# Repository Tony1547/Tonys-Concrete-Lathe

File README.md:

# Tonys-Concrete-Lathe #
Lathe but 3d prints &amp; concrete

Special thanks Mark Harris to for creating this open source design which I based my H-brdge motor driver off of, heres the link to his blog of his design and his git hub page:

- https://resources.altium.com/p/100a-12v-h-bridge-project

- https://github.com/issus

and another big thanks to Chris Borge for inspiring this project with his "I Printed A Better Lathe" video

- https://www.youtube.com/watch?v=6Js8erWbsDQ

---- 

This is the lathe I have been desingning for the past 2-ish months, I was initially inspired by Chris Borge a Youtuber who focuses on creating machines to help with his own personal projects and 3d-prints that are filled with concrete. Now, this is the second iteration design, not becuase I built a first lathe but because the first time I tried to put everything into CAD it all started to look like a toy and I thought I could do better, which I'm glad that I did. Which now leads to the vesion you see above and below this bar of text.

Something I initially struggled with was finding a way to connect all the parts toghether, in my initial design I tried to make each 3d printed part interlock with dove-tails but that soon became much more problematic than was needed. I solved this problem with allowing an open hole from part to part on the inside to connect all parts into this chamber that I hope keeps everything together once the concrete dries. 

For the reason that I built this project, I want to have better manufacturing capabilities at home, and having a machine that allows me to focus on one type of part (being conical and cylindrical parts) I think will allow me to have better projects in the future.

Journal: https://fallout.hackclub.com/projects/1831

# Assembly
Hi! if you're reading this, your either reading to review, see whats going on, or interested in building this project yourself.

- The first step in creating the lathe is set up, make sure you have all hardware, bearings, belt &amp; pulley's, 3d prints, PCB, concrete, and extrusion material on hand

- Make sure to use heated inserts before this next step and to cover anny holes which may clog with concrete with tape.

- The next step is is to assemble the base, head stock, and upper walls seperately, glue them with each other inside those groups and let it rest (you may want to put the hardware, extrusions, and linear slide in for the base before glueing), after the glue is done drying, you may start off by pouring concrete into the base.

- After concrete has been poured into the base (process can change depending on the part) you can now assemble and put-in the top of the lathe wall and headstock and fill those with conctete as well, if you can find a power tool to vibrate the lathe to allow air bubbles to escape then use that as well too.

-After allowing the concrete to dry, you may add on the tool carriage and screw on the PCB to to the lathe, make sure to wire and test and you should have a functional lathe!

Remember when using the lathe, the part should be spining to where it's coming down onto the tool and not the other way around.

Currently the lathe is run by either two buttons on the back for foward/revevrse but the option for external control was also given, so with an off board micro controller you could be very exact with how you want this thing to spin. (I plan to use an off board MCU when possible)

Onshape: https://cad.onshape.com/documents/8fec9f06f8e21e4e1cabcead/w/11b83efad18e13bc0ea2df61/e/2ea9e03e0bad05dbdf986923?page=2&email=ah404751%40g.risd.org&renderMode=0&uiState=6a30d3e5ff79be115d0b7c52

# BOM

Google Sheet: https://docs.google.com/spreadsheets/d/1Rf3SECQ2E7oCPYBzGCeOMEVJCDXd7yVN8Rsrsj5uyMo/edit?usp=sharing 

| Index   | Vendor      | Description                        | Quantity                  | Unit Price($)             | Extended Price($) | Product Link                                                                                                                                                                                                                                                                                                                                                                                                                                                                                                                                                                                                                                                         |      |          |     |          |               |                   |                                                    |
|---------|-------------|------------------------------------|---------------------------|---------------------------|-------------------|----------------------------------------------------------------------------------------------------------------------------------------------------------------------------------------------------------------------------------------------------------------------------------------------------------------------------------------------------------------------------------------------------------------------------------------------------------------------------------------------------------------------------------------------------------------------------------------------------------------------------------------------------------------------|------|----------|-----|----------|---------------|-------------------|----------------------------------------------------|
| 1       | Ali Express | 5x13x4mm Flanged Bearing           | 10                        | $0.51                     | $5.06             | https://www.aliexpress.us/item/3256803908686248.html?spm=a2g0o.productlist.main.1.596dOhTVOhTVzT&algo_pvid=de089ae8-5913-49c9-acd4-66d24c447885&algo_exp_id=de089ae8-5913-49c9-acd4-66d24c447885-0&pdp_ext_f=%7B%22order%22%3A%22852%22%2C%22eval%22%3A%221%22%2C%22fromPage%22%3A%22search%22%7D&pdp_npi=6%40dis%21USD%215.08%210.99%21%21%215.08%210.99%21%402101e8f317815960924911388ed342%2112000028970871486%21sea%21US%216805647519%21ABX%211%210%21n_tag%3A-29910%3Bd%3A3a14889%3Bm03_new_user%3A-29895%3BpisId%3A5000000207262921&curPageLogUid=q1H4CezHkX5N&utparam-url=scene%3Asearch%7Cquery_from%3A%7Cx_object_id%3A1005004095001000%7C_p_origin_prod%3A |      |          |     |          |               |                   |                                                    |
| 2       | Ali Express | 140T GT2 10mm belt                 | 1                         | $3.78                     | $3.78             | https://www.aliexpress.us/item/3256806906134014.html?spm=a2g0o.detail.0.0.6dc6bKhdbKhdvN&mp=1&pdp_npi=6%40dis%21USD%21USD+3.78%21USD+3.78%21%21USD+3.78%21%21%21%402101e2b017815961262145354ef2ca%2112000039378829177%21ct%21US%216805647519%21%211%210%21&gatewayAdapt=glo2usa                                                                                                                                                                                                                                                                                                                                                                                      |      |          |     |          |               |                   |                                                    |
| 3       | Ali Express | ER25 8mm Collet                    | 1                         | $6.25                     | $6.25             | https://www.aliexpress.us/item/2255800773550976.html?spm=a2g0o.detail.0.0.2c62U9tFU9tFKE&mp=1&pdp_npi=6%40dis%21USD%21USD+14.89%21USD+6.25%21%21USD+6.25%21%21%21%402101e07217815966367485977edac3%2110000012670797470%21ct%21US%216805647519%21%211%210%21&gatewayAdapt=glo2usa                                                                                                                                                                                                                                                                                                                                                                                     |      |          |     |          |               |                   |                                                    |
| 4       | Ali Express | 50mm Chuck                         | 1                         | $20.01                    | $20.01            | https://www.aliexpress.us/item/3256809251348831.html?spm=a2g0o.detail.0.0.6816AbePAbeP4V&mp=1&pdp_npi=6%40dis%21USD%21USD+40.01%21USD+20.01%21%21USD+20.01%21%21%21%402101e07217815966813736979edac3%2112000049098833905%21ct%21US%216805647519%21%211%210%21&gatewayAdapt=glo2usa                                                                                                                                                                                                                                                                                                                                                                                   |      |          |     |          |               |                   |                                                    |
| 5       | Ali Express | 30T + 60T Pulley's                 | 2                         | $9.47                     | $18.94            | https://www.aliexpress.us/item/3256805897449052.html?spm=a2g0o.detail.0.0.3809lnEelnEeAL&mp=1&pdp_npi=6%40dis%21USD%21USD+31.56%21USD+18.94%21%21USD+18.94%21%21%21%402101e07217815967189997474edac3%2112000035654690827%21ct%21US%216805647519%21%211%210%21&gatewayAdapt=glo2usa                                                                                                                                                                                                                                                                                                                                                                                   |      |          |     |          |               |                   |                                                    |
| 6       | Ali Express | 20x47x19.25 Tapered Roller Bearing | 2                         | $3.59                     | $7.18             | https://www.aliexpress.us/item/3256802472132854.html?spm=a2g0o.detail.0.0.54d2qkcUqkcUjC&mp=1&pdp_npi=6%40dis%21USD%21USD+11.04%21USD+7.18%21%21USD+7.18%21%21%21%402101e07217815967512357791edac3%2112000021590990791%21ct%21US%216805647519%21%211%210%21&gatewayAdapt=glo2usa                                                                                                                                                                                                                                                                                                                                                                                     |      |          |     |          |               |                   |                                                    |
| 7       | Ali Express | C20-ER25-150L Spindle              | 1                         | $15.84                    | $15.84            | https://www.aliexpress.us/item/3256801168631119.html?spm=a2g0o.detail.0.0.a1caNKVQNKVQHK&mp=1&pdp_npi=6%40dis%21USD%21USD+26.40%21USD+15.84%21%21USD+15.84%21%21%21%402101e07217815967927098166edac3%2112000025664963300%21ct%21US%216805647519%21%211%210%21&gatewayAdapt=glo2usa                                                                                                                                                                                                                                                                                                                                                                                   |      |          |     |          |               |                   |                                                    |
| 8       | Tnutz       | 2020 Extrusion                     | 2                         | $1.33                     | $2.66             | https://www.tnutz.com/product/exm-2020/?attribute_pa_length-in=12&attribute_pa_fractional-length=0-000                                                                                                                                                                                                                                                                                                                                                                                                                                                                                                                                                               |      |          |     |          |               |                   |                                                    |
| 9       | Tnutz       | Tapped 2020 Extrusion              | 2                         | $0.77                     | $1.54             | https://www.tnutz.com/product/exm-2020/?attribute_pa_length-in=3&attribute_pa_fractional-length=0-938-15-16                                                                                                                                                                                                                                                                                                                                                                                                                                                                                                                                                          |      |          |     |          |               |                   |                                                    |
| 10      | Tnutz       | M3 T-Nut                           | 40                        | $0.40                     | $16.00            | https://www.tnutz.com/product/st-020/?attribute_pa_thread-size=m3-x-0-5                                                                                                                                                                                                                                                                                                                                                                                                                                                                                                                                                                                              |      |          |     |          |               |                   |                                                    |
| 11      | Grainger    | 1M M4 Threaded Rod                 | 1                         | $2.35                     | $2.35             | https://www.grainger.com/product/Fully-Threaded-Rod-M4x0-70-25DM24                                                                                                                                                                                                                                                                                                                                                                                                                                                                                                                                                                                                   |      |          |     |          |               |                   |                                                    |
| 12      | Grainger    | M4 Nuts                            | 100                       | $0.03                     | $2.94             | https://www.grainger.com/product/Hex-Nut-Std-Hex-6CA71                                                                                                                                                                                                                                                                                                                                                                                                                                                                                                                                                                                                               |      |          |     |          |               |                   |                                                    |
| 13      | Amazon      | M3 Nuts                            | 150                       | $0.03                     | $4.99             | https://www.amazon.com/gp/product/B08N68W9SP/ref=ox_sc_act_title_1?smid=A2BPIUS9TNF8L5&psc=1                                                                                                                                                                                                                                                                                                                                                                                                                                                                                                                                                                         |      |          |     |          |               |                   |                                                    |
| 14      | Amazon      | 2 Part Epoxy                       | 1                         | $5.97                     | $5.97             | https://www.amazon.com/gp/product/B001Z3C3AG/ref=ox_sc_act_title_2?smid=ATVPDKIKX0DER&psc=1                                                                                                                                                                                                                                                                                                                                                                                                                                                                                                                                                                          |      |          |     |          |               |                   |                                                    |
| 15      | Amazon      | M3 Brass Inserts                   | 100                       | $0.05                     | $4.99             | https://www.amazon.com/gp/product/B0FM45X5TD/ref=ox_sc_act_title_3?smid=AIMQC13A5VC4X&psc=1                                                                                                                                                                                                                                                                                                                                                                                                                                                                                                                                                                          |      |          |     |          |               |                   |                                                    |
| 16      | Amazon      | M4 Brass Inserts                   | 60                        | $0.08                     | $4.83             | https://www.amazon.com/gp/product/B0DFWVT6XT/ref=ox_sc_act_title_4?smid=A3FX0IVQQTIB98&psc=1                                                                                                                                                                                                                                                                                                                                                                                                                                                                                                                                                                         |      |          |     |          |               |                   |                                                    |
| 17      | Amazon      | M3x10mm Screws                     | 120                       | $0.03                     | $3.79             | https://www.amazon.com/gp/product/B0F7LKRV5G/ref=ox_sc_act_title_5?smid=A2W3XYA7BVZZ2U&psc=1                                                                                                                                                                                                                                                                                                                                                                                                                                                                                                                                                                         |      |          |     |          |               |                   |                                                    |
| 18      | Amazon      | M3x25mm Screws                     | 40                        | $0.16                     | $6.39             | https://www.amazon.com/gp/product/B08R8J3175/ref=ox_sc_act_title_6?smid=A2XHUR0CG3X852&psc=1                                                                                                                                                                                                                                                                                                                                                                                                                                                                                                                                                                         |      |          |     |          |               |                   |                                                    |
| 19      | Amazon      | M3x22mm Screws                     | 50                        | $0.13                     | $6.29             | https://www.amazon.com/gp/product/B0FLYG7WZ7/ref=ox_sc_act_title_7?smid=A2SQCOYQC9C41K&psc=1                                                                                                                                                                                                                                                                                                                                                                                                                                                                                                                                                                         |      |          |     |          |               |                   |                                                    |
| 20      | REV         | #10-32 Socket head Screw           | 50                        | $0.11                     | $5.50             | https://www.revrobotics.com/10-32-Socket-Head-Screws/                                                                                                                                                                                                                                                                                                                                                                                                                                                                                                                                                                                                                |      |          |     |          |               |                   |                                                    |
| 21      | AndyMark    | Cim Motor                          | 1                         | $43.00                    | $43.00            | https://andymark.com/products/2-5-in-cim-motor?variant=44497393680556                                                                                                                                                                                                                                                                                                                                                                                                                                                                                                                                                                                                |      |          |     |          |               |                   |                                                    |
| 22      | Ali Express | MGN9 300mm rail                    | 1                         | $16.77                    | $16.77            | https://www.aliexpress.us/item/2251832586981749.html?spm=a2g0o.productlist.main.2.3f0736ST36STyg&algo_pvid=6c119559-49bd-4699-aa8a-5593d0031d4d&algo_exp_id=6c119559-49bd-4699-aa8a-5593d0031d4d-1&pdp_ext_f=%7B%22order%22%3A%221106%22%2C%22eval%22%3A%221%22%2C%22fromPage%22%3A%22search%22%7D&pdp_npi=6%40dis%21USD%2113.34%218.57%21%21%2113.34%218.57%21%402103129f17819408540613048e6996%2165514571337%21sea%21US%216805647519%21ABX%211%210%21n_tag%3A-29910%3Bd%3A3a14889%3Bm03_new_user%3A-29895%3BpisId%3A5000000208023469&curPageLogUid=DVcxAF6Fx4cn&utparam-url=scene%3Asearch%7Cquery_from%3A%7Cx_object_id%3A32773296501%7C_p_origin_prod%3A         |      |          |     |          |               |                   |                                                    |
| 23      | Home Depot  | Concrete                           | 1                         | $4.48                     | $4.48             | https://www.homedepot.com/p/Quikrete-60-lb-Concrete-Mix-110160/100318478                                                                                                                                                                                                                                                                                                                                                                                                                                                                                                                                                                                             |      |          |     |          |               |                   |                                                    |
|         |             |                                    |                           | Total =                   | $209.55           |                                                                                                                                                                                                                                                                                                                                                                                                                                                                                                                                                                                                                                                                      |      |          |     |          |               |                   |                                                    |
|         |             |                                    |                           |                           |                   |                                                                                                                                                                                                                                                                                                                                                                                                                                                                                                                                                                                                                                                                      |      |          |     |          |               |                   |                                                    |
| Index   | LCSC#       | MPN                                | Manufacturer              | Package                   |                   | Description                                                                                                                                                                                                                                                                                                                                                                                                                                                                                                                                                                                                                                                          | RoHS | Quantity | MOQ | Multiple | Unit Price($) | Extended Price($) | Product Link                                       |
| 1       | C309795     | HIP4081AIBZT                       | RENESAS                   | SOIC-20-300mil            |                   | Full-Bridge MOSFET 100mA 10ns 10ns 100mA SOIC-20-300mil Full Half-Bridge (H Bridge) Drivers RoHS                                                                                                                                                                                                                                                                                                                                                                                                                                                                                                                                                                     | yes  | 1        | 1   | 1        | 4.3088        | 4.31              | https://www.lcsc.com/product-detail/C309795.html   |
| 2       | C29936      | CL10B105KA8NNNC                    | Samsung Electro-Mechanics | 603                       |                   | 1uF ±10% 25V Ceramic Capacitor X7R 0603                                                                                                                                                                                                                                                                                                                                                                                                                                                                                                                                                                                                                              | yes  | 50       | 50  | 50       | 0.0219        | 1.1               | https://www.lcsc.com/product-detail/C29936.html    |
| 3       | C22364900   | CDBA340L-G                         | Comchip                   | DO-214AC                  |                   | Diode 40V 3A Surface Mount DO-214AC                                                                                                                                                                                                                                                                                                                                                                                                                                                                                                                                                                                                                                  | yes  | 8        | 1   | 1        | 1.1112        | 8.89              | https://www.lcsc.com/product-detail/C22364900.html |
| 4       | C18724377   | MF0S4FF200JA50                     | UNI-ROYAL                 | Through Hole,D1.9xL3.3mm  |                   | 20Ω 250mW Metal Film Resistor ±50ppm/℃ ±1% Through Hole,D1.9xL3.3mm Through Hole Resistors RoHS                                                                                                                                                                                                                                                                                                                                                                                                                                                                                                                                                                      | yes  | 50       | 50  | 50       | 0.005         | 0.25              | https://www.lcsc.com/product-detail/C18724377.html |
| 5       | C9807       | CL31A106KAHNNNE                    | Samsung Electro-Mechanics | 1206                      |                   | 10uF ±10% 25V Ceramic Capacitor X5R 1206                                                                                                                                                                                                                                                                                                                                                                                                                                                                                                                                                                                                                             | yes  | 10       | 10  | 10       | 0.0937        | 0.94              | https://www.lcsc.com/product-detail/C9807.html     |
| 6       | C24497      | CL31B104KBCNNNC                    | Samsung Electro-Mechanics | 1206                      |                   | 100nF ±10% 50V Ceramic Capacitor X7R 1206                                                                                                                                                                                                                                                                                                                                                                                                                                                                                                                                                                                                                            | yes  | 20       | 20  | 20       | 0.019         | 0.38              | https://www.lcsc.com/product-detail/C24497.html    |
| 7       | C553224     | PSMN1R5-25MLHX                     | Nexperia                  | SOT-1210                  |                   | N-Channel 25V 150A 106W SOT-1210                                                                                                                                                                                                                                                                                                                                                                                                                                                                                                                                                                                                                                     | yes  | 8        | 1   | 1        | 3.6382        | 29.11             | https://www.lcsc.com/product-detail/C553224.html   |
| 8       | C3454390    | MFR-25FBF52-2K2                    | YAGEO                     | Through Hole,D2.4xL6.3mm  |                   | 2.2kΩ 250mW Metal Film Resistor ±100ppm/℃ ±1% Through Hole,D2.4xL6.3mm Through Hole Resistors RoHS                                                                                                                                                                                                                                                                                                                                                                                                                                                                                                                                                                   | yes  | 50       | 50  | 50       | 0.0195        | 0.98              | https://www.lcsc.com/product-detail/C3454390.html  |
| 9       | C330747     | TJ-L3FYTGHKMCGSFLC7K-A5            | TOGIALED                  | Through Hole,D=3mm        |                   | LED Indication - Discrete Through Hole,D=3mm                                                                                                                                                                                                                                                                                                                                                                                                                                                                                                                                                                                                                         | yes  | 20       | 20  | 20       | 0.0292        | 0.58              | https://www.lcsc.com/product-detail/C330747.html   |
| 10      | C559114     | MHL5013UBDWT                       | MEIHUA                    | Through Hole,D=5mm        |                   | Blue 470nm LED Indication - Discrete 3.2V Through Hole,D=5mm                                                                                                                                                                                                                                                                                                                                                                                                                                                                                                                                                                                                         | yes  | 10       | 10  | 10       | 0.0523        | 0.52              | https://www.lcsc.com/product-detail/C559114.html   |
| 11      | C61299      | CFR0W4J0103A50                     | UNI-ROYAL                 | Through Hole,D2.2xL6.5mm  |                   | 10kΩ 250mW 250V Carbon Film Resistor ±450ppm/℃ ±5% Through Hole,D2.2xL6.5mm Through Hole Resistors RoHS                                                                                                                                                                                                                                                                                                                                                                                                                                                                                                                                                              | yes  | 50       | 50  | 50       | 0.0125        | 0.63              | https://www.lcsc.com/product-detail/C61299.html    |
| 12      | C113892     | CC1206KKX7R0BB224                  | YAGEO                     | 1206                      |                   | 220nF ±10% 100V Ceramic Capacitor X7R 1206                                                                                                                                                                                                                                                                                                                                                                                                                                                                                                                                                                                                                           | yes  | 20       | 20  | 20       | 0.0404        | 0.81              | https://www.lcsc.com/product-detail/C113892.html   |
| 13      | C843877     | WSHP28182L000FEA                   | VISHAY                    | 2818                      |                   | 2mΩ 10W ±1% ±200ppm/℃ 2818 Chip Resistor - Surface Mount RoHS                                                                                                                                                                                                                                                                                                                                                                                                                                                                                                                                                                                                        | yes  | 4        | 1   | 1        | 2.3567        | 9.43              | https://www.lcsc.com/product-detail/C843877.html   |
| 14      | C119483     | MF1W-1KΩ±1% T                      | CCO(Chian Chia Elec)      | Through Hole,D4.5xL11.5mm |                   | 1kΩ 1W 350V Metal Film Resistor ±100ppm/℃ ±1% Through Hole,D4.5xL11.5mm Through Hole Resistors RoHS                                                                                                                                                                                                                                                                                                                                                                                                                                                                                                                                                                  | yes  | 10       | 10  | 10       | 0.0496        | 0.5               | https://www.lcsc.com/product-detail/C119483.html   |
| 15      | C707749     | KF88SA-16.0-2P                     | Cixi Kefa Elec            | Through Hole,P=16mm       |                   | 2 Position Barrier Block Connector 6~14 AWG 1000V 76A Through Hole                                                                                                                                                                                                                                                                                                                                                                                                                                                                                                                                                                                                   | yes  | 2        | 1   | 1        | 0.8305        | 1.66              | https://www.lcsc.com/product-detail/C707749.html   |
| 16      | C435835     | LDL1117S33R                        | ST                        | SOT-223-4                 |                   | 3.3V Positive Fixed SOT-223-4 Voltage Regulators - Linear, Low Drop Out (LDO) Regulators RoHS                                                                                                                                                                                                                                                                                                                                                                                                                                                                                                                                                                        | yes  | 5        | 5   | 5        | 0.2132        | 1.07              | https://www.lcsc.com/product-detail/C435835.html   |
| 17      | C158012     | B2B-XH-A(LF)(SN)                   | JST                       | Through Hole,P=2.5mm      |                   | Connector Header 2 position 2.5mm Pitch 3A Through Hole -25℃~+85℃                                                                                                                                                                                                                                                                                                                                                                                                                                                                                                                                                                                                    | yes  | 20       | 20  | 20       | 0.0405        | 0.81              | https://www.lcsc.com/product-detail/C158012.html   |
| 18      | C144397     | B6B-XH-A(LF)(SN)                   | JST                       | Through Hole,P=2.5mm      |                   | Connector Header 6 position 2.5mm Pitch 3A Through Hole -25℃~+85℃                                                                                                                                                                                                                                                                                                                                                                                                                                                                                                                                                                                                    | yes  | 5        | 5   | 5        | 0.0917        | 0.46              | https://www.lcsc.com/product-detail/C144397.html   |
| 19      | C455280     | TS-1088R-02026                     | XUNPU                     | SMD,4x3mm                 |                   | Tactile Switch SPST 2mm 3.9mm x 2.93mm Surface Mount                                                                                                                                                                                                                                                                                                                                                                                                                                                                                                                                                                                                                 | yes  | 10       | 10  | 10       | 0.0597        | 0.6               | https://www.lcsc.com/product-detail/C455280.html   |
|         |             |                                    |                           |                           |                   |                                                                                                                                                                                                                                                                                                                                                                                                                                                                                                                                                                                                                                                                      |      |          |     |          |               | Total = 63.42     |                                                    |
| Total = | $272.97     |                                    |                           |                           |                   |                                                                                                                                                                                                                                                                                                                                                                                                                                                                                                                                                                                                                                                                      |      |          |     |          |               |                   |                                                    |

# PCB Schematic

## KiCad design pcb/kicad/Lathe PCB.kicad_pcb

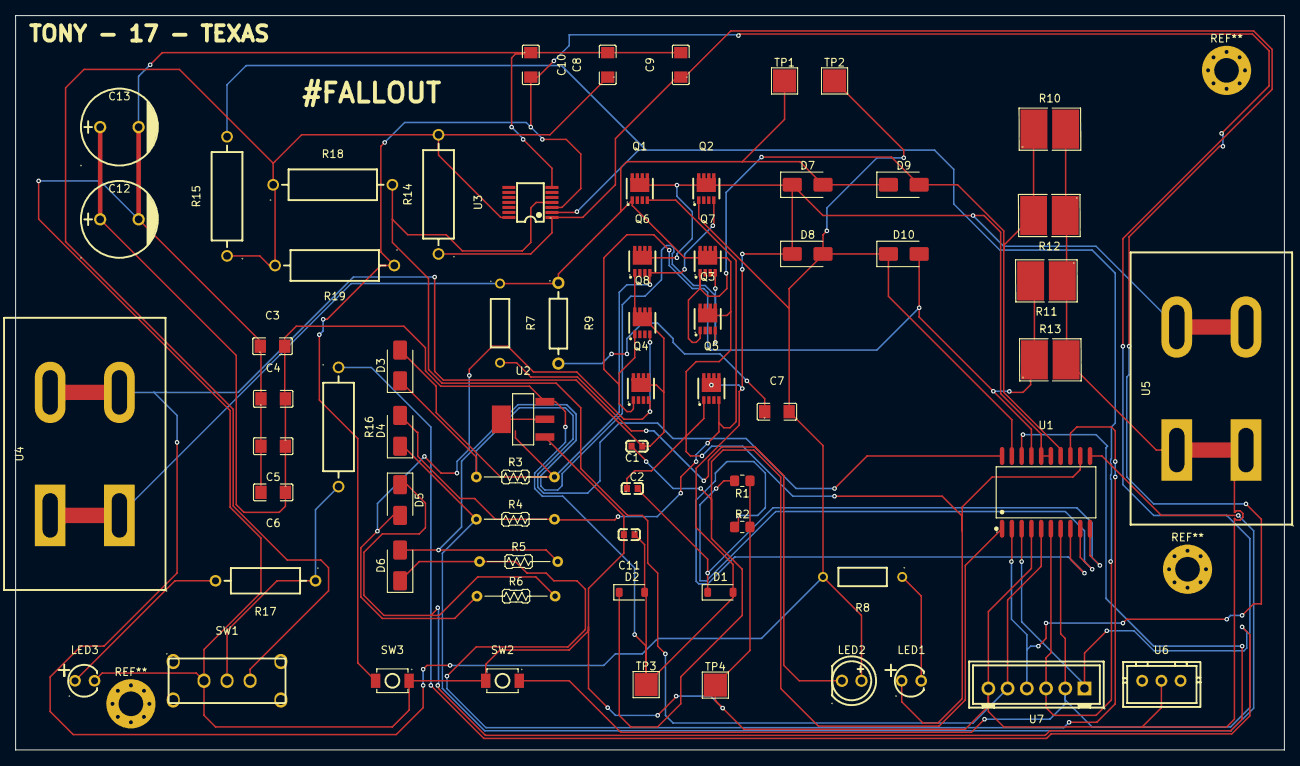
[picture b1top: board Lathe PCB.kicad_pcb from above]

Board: 2 copper layers, 165.0 x 95.5 mm, 67 parts (0 on the bottom side), 30 nets.

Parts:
C1, C2, C11: 1uf; C0603
C3, C4: 10uf; C1206
C5, C6, C8, C9, C10: 0.1uf; C1206
C7: 0.22 uf; C1206
C12, C13: ERS1HM331G13OT; CAP-TH_BD10.0-P5.00-D0.6-FD
D1, D2: 1N4148W; D_SOD-123
D3, D4, D5, D6, D7, D8, D9, D10: CDBA340L-G; D_SMA
LED1, LED3: GREEN; LED-TH_BD3.8-P2.54-FD
LED2: BLUE; LED-TH_BD5.0-P2.54-L-RD_WHITE
Q1, Q2, Q3, Q4, Q5, Q6, Q7, Q8: PSMN1R5-25MLHX; SOT-1210_L3.3-W2.6-P0.65-LS3.3-BL
R1, R2: 75k ohms; R_0805_2012Metric_Pad1.20x1.40mm_HandSolder
R3, R4, R5, R6: 20ohms; R_Axial_DIN0204_L3.6mm_D1.6mm_P10.16mm_Horizontal
R7, R8: 2.2k ohm; RES-TH_BD2.4-L6.3-P10.30-D0.6
R9: 10k ohms; RES-TH_BD2.2-L6.5-P10.50-D0.6
R10, R11, R12, R13: 2 mOhms; R2818
R14, R15, R16, R18, R19: 1 kOmhs; RES-TH_BD4.0-L11.5-P15.50-D0.7
R17: 120 Ohms; RES-TH_BD3.3-L9.0-P13.00-D0.6
SW1: SK-12F17-G7; SW-TH_SK-12F17-G7
SW2, SW3: TS-1088R-02026; SW-SMD_L3.9-W3.0-P4.45
TP1, TP2, TP3, TP4: TestPoint; TestPoint_Pad_3.0x3.0mm
U1: HIP4081AIBZT; SOIC-20_L13.0-W7.6-P1.27-LS10.3-BL
U2: LDL1117S33R; SOT-223-4_L6.5-W3.5-P2.30-LS7.0-BR
U3: SN74LVC14APWRG4; TSSOP-14_L5.0-W4.4-P0.65-LS6.4-BL
U4, U5: KF88SA-16.0-2P; CONN-TH_KF88SA-16.0-2P
U6: B3B-XH-A; CONN-TH_3P-P2.50_A2501WV2-3P
U7: B6B-XH-A; CONN-TH_6P-P2.50_B6B-XH-A-LF-SN

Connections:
+3.3V: C8.1, R14.2, R15.1, R18.1, R19.2, SW1.3, U3.14 (VCC)
+12V: C3.2, C4.2, C5.1, C6.1, C11.1, C12.1, C13.1, D1.2 (A), D2.2 (A), D7.1 (K), D8.1 (K), Q1.5 (D), Q2.5 (D), Q5.5 (D), Q6.5 (D), TP3.1 (1_1), U1.15 (VCC), U1.16 (VDD), U2.3 (VIN), U5.2
/BST B: C2.2, D2.1 (K), U1.1 (BHB)
/BSTA: C1.2, D1.1 (K), U1.10 (AHB)
EN: R16.1, U1.3 (DIS), U7.1
GATEH A: D4.2 (A), Q1.4 (G), Q5.4 (G), R4.2
GATEH B: D3.2 (A), Q2.4 (G), Q6.4 (G), R3.2
GATEL A: D6.2 (A), Q3.4 (G), Q7.4 (G), R5.2
GATEL B: D5.2 (A), Q4.4 (G), Q8.4 (G), R6.1
GND: C3.1, C4.1, C5.2, C6.2, C8.2, C9.2, C10.1, C11.2, C12.2, C13.2, LED3.2, R1.1, R2.2, R10.2, R11.1, R12.1, R13.2, SW1.1, SW2.1, SW3.2, TP4.1 (1_1), U1.4 (VSS), U2.1 (GND), U3.7 (GND), U5.1, U6.2, U7.6
HIGHIN A: C9.1, R14.1, SW2.2, U1.7 (AHI), U3.1 (1A), U7.2
HIGHIN B: C10.2, R19.1, SW3.1, U1.2 (BHI), U3.3 (2A), U7.4
HIGHSRC A: C1.1, D7.2 (A), D9.1 (K), LED1.1, Q1.1 (S), Q3.5 (D), Q5.1 (S), Q7.5 (D), R7.1, R9.1, TP1.1 (1_1), U1.12 (AHS), U4.1
HIGHSRC B: C2.1, C7.2, D8.2 (A), D10.1 (K), LED2.2 (+), Q2.1 (S), Q4.5 (D), Q6.1 (S), Q8.5 (D), R8.2, TP2.1 (1_1), U1.19 (BHS), U4.2
LOWIN A: R15.2, U1.6 (ALI), U3.2 (1Y), U7.3
LOWIN B: R18.2, U1.5 (BLI), U3.4 (2Y), U7.5
LOWSRC A: D9.2 (A), Q3.1 (S), Q7.1 (S), R10.1, R12.2, U1.14 (ALS)
LOWSRC B: D10.2 (A), Q4.1 (S), Q8.1 (S), R11.2, R13.1, U1.17 (BLS)
unnamed: C7.1, R9.2
unnamed: D3.1 (K), R3.1, U1.20 (BHO)
unnamed: D4.1 (K), R4.1, U1.11 (AHO)
unnamed: D5.1 (K), R6.2, U1.18 (BLO)
unnamed: D6.1 (K), R5.1, U1.13 (ALO)
unnamed: LED1.2, R8.1
unnamed: LED2.1 (-), R7.2
unnamed: LED3.1, R17.2
unnamed: R16.2, R17.1, SW1.2
unnamed: R2.1, U1.8 (HDEL)
unnamed: R1.2, U1.9 (LDEL)
unnamed: U2.2 (VOUT), U2.4 (VOUT)

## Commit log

2026-06-15 Gerber and Step files added
2026-06-16 Update README.md
    Added images to README for visual reference.
2026-06-16 organize stl files
2026-06-16 Image folder added
2026-06-16 rename folders
2026-06-16 added kicad files
2026-06-16 Add Lathe BOM.csv
2026-06-20 updated organization
2026-06-20 Git LFS
2026-06-20 update bom
2026-06-20 renaming
2026-06-21 rename for clarity
2026-06-21 rename for clarity
    stl folder
2026-06-23 replaced stl with step
